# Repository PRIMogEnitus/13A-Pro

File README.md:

# 13A Pro Macropad
 
 A simple 13-keys macropad, created with the aim of maximum functionality with relatively low cost to build,
 And yes the "Pro" in the name stands for nothing, i typed it wrong, and i'm too lazy to change everything again.
# Features
 13A Pro features small and compact size to carry almost anywhere without sacrificing its functionality,
 the main downside is that the 13A Pro doesn't have a soft reset key, despite that as it's using Arduino as the MCU,
 the layout is customizable depending on needs.
# Layout

Standard layout for the 13A Pro (the first layer is the top legends, where the second layer is the bottom legends)
# DISCLAIMER
 The 13A Pro macropad hasn't tested yet, so if you decide to build one, then proceed at your own risk.

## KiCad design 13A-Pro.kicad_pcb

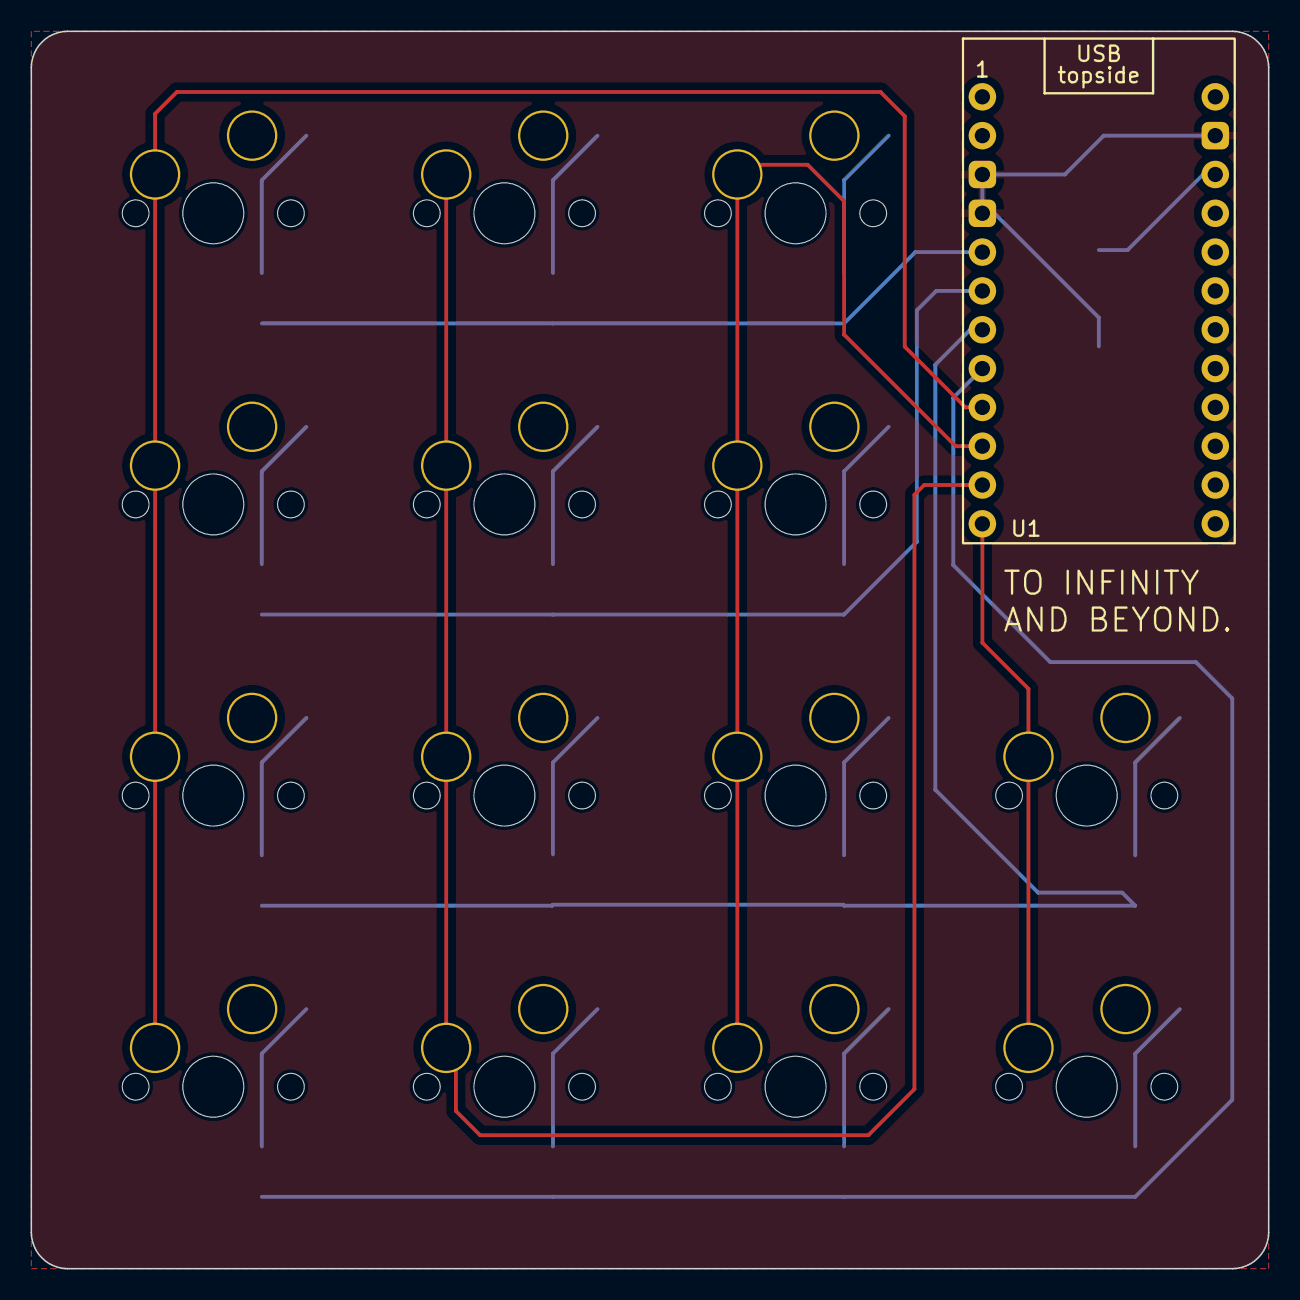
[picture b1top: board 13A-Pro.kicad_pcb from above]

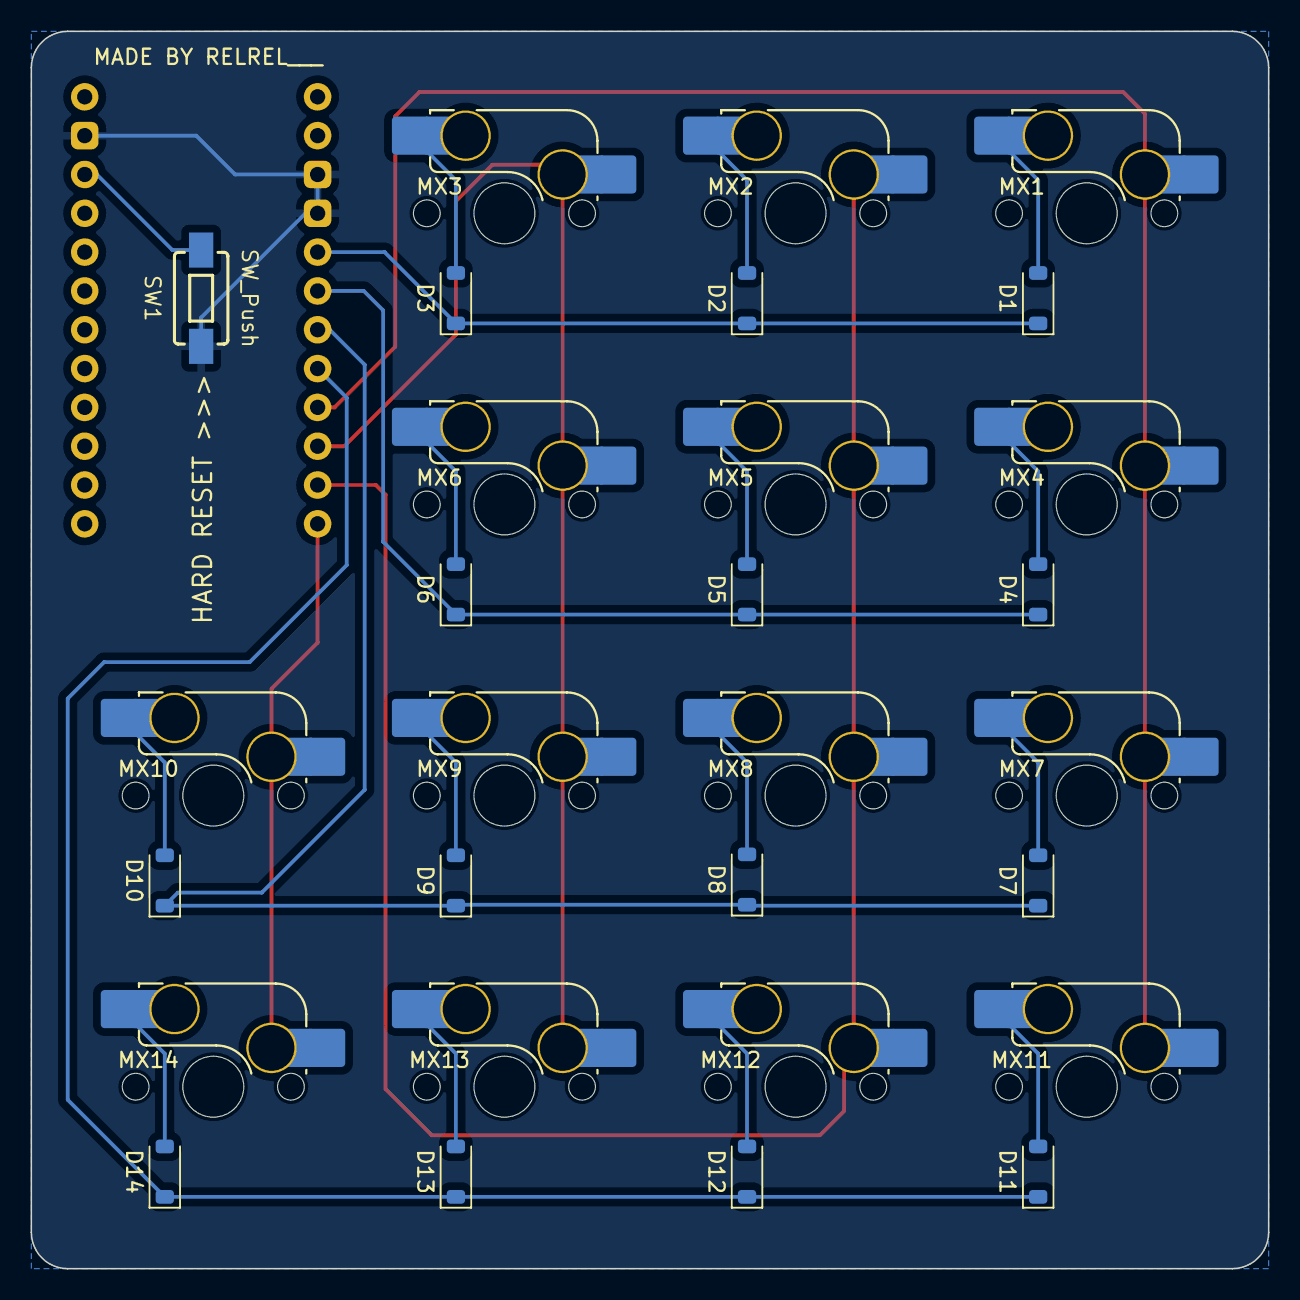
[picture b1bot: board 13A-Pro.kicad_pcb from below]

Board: 2 copper layers, 81.0 x 81.0 mm, 30 parts (29 on the bottom side), 24 nets.

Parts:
D1, D2, D3, D4, D5, D6, D7, D8, D9, D10, D11, D12, D13, D14: D_Small; D_SOD-123
MX1, MX2, MX3, MX4, MX5, MX6, MX7, MX8, MX9, MX10, MX11, MX12, MX13, MX14: MX_SW_HS; SW_MX_HS_1u
SW1: SW_Push; TACTILE_SWITCH_SMD_6.0X3.5MM
U1: ProMicro; ProMicro_USBup

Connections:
COL0: MX1.1, MX4.1, MX7.1, MX11.1, U1.9 (D7)
COL1: MX2.1, MX5.1, MX8.1, MX12.1, U1.11 (B4)
COL2: MX3.1, MX6.1, MX9.1, MX13.1, U1.10 (E6)
COL3: MX10.1, MX14.1, U1.12 (B5)
GND: SW1.1, U1.3 (GND), U1.4 (GND), U1.14 (GND)
unnamed: D1.2 (A), MX1.2
unnamed: D2.2 (A), MX2.2
unnamed: D3.2 (A), MX3.2
unnamed: D4.2 (A), MX4.2
unnamed: D5.2 (A), MX5.2
unnamed: D6.2 (A), MX6.2
unnamed: D7.2 (A), MX7.2
unnamed: D8.2 (A), MX8.2
unnamed: D9.2 (A), MX9.2
unnamed: D10.2 (A), MX10.2
unnamed: D11.2 (A), MX11.2
unnamed: D12.2 (A), MX12.2
unnamed: D13.2 (A), MX13.2
unnamed: D14.2 (A), MX14.2
unnamed: SW1.2, U1.15 (RST)
ROW0: D1.1 (K), D2.1 (K), D3.1 (K), U1.5 (D1)
ROW1: D4.1 (K), D5.1 (K), D6.1 (K), U1.6 (D0)
ROW2: D7.1 (K), D8.1 (K), D9.1 (K), D10.1 (K), U1.7 (D4)
ROW3: D11.1 (K), D12.1 (K), D13.1 (K), D14.1 (K), U1.8 (C6)

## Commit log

2024-08-24 Initialize Project
2024-08-24 Footprint and Library update
2024-08-24 Schematics update
2024-08-24 Library revision and Footprint update
2024-08-24 Footprints assigning
2024-08-24 PCB Update
2024-08-24 PCB Update ver 1.0
2024-08-25 Case, PCB, Firmware update
2024-08-25 Case, Firmware update
2024-08-25 Some file removed
2024-08-25 PCB update, and file removal
2024-08-25 Added BOM
2024-08-25 Save update
2024-08-25 Latest update
